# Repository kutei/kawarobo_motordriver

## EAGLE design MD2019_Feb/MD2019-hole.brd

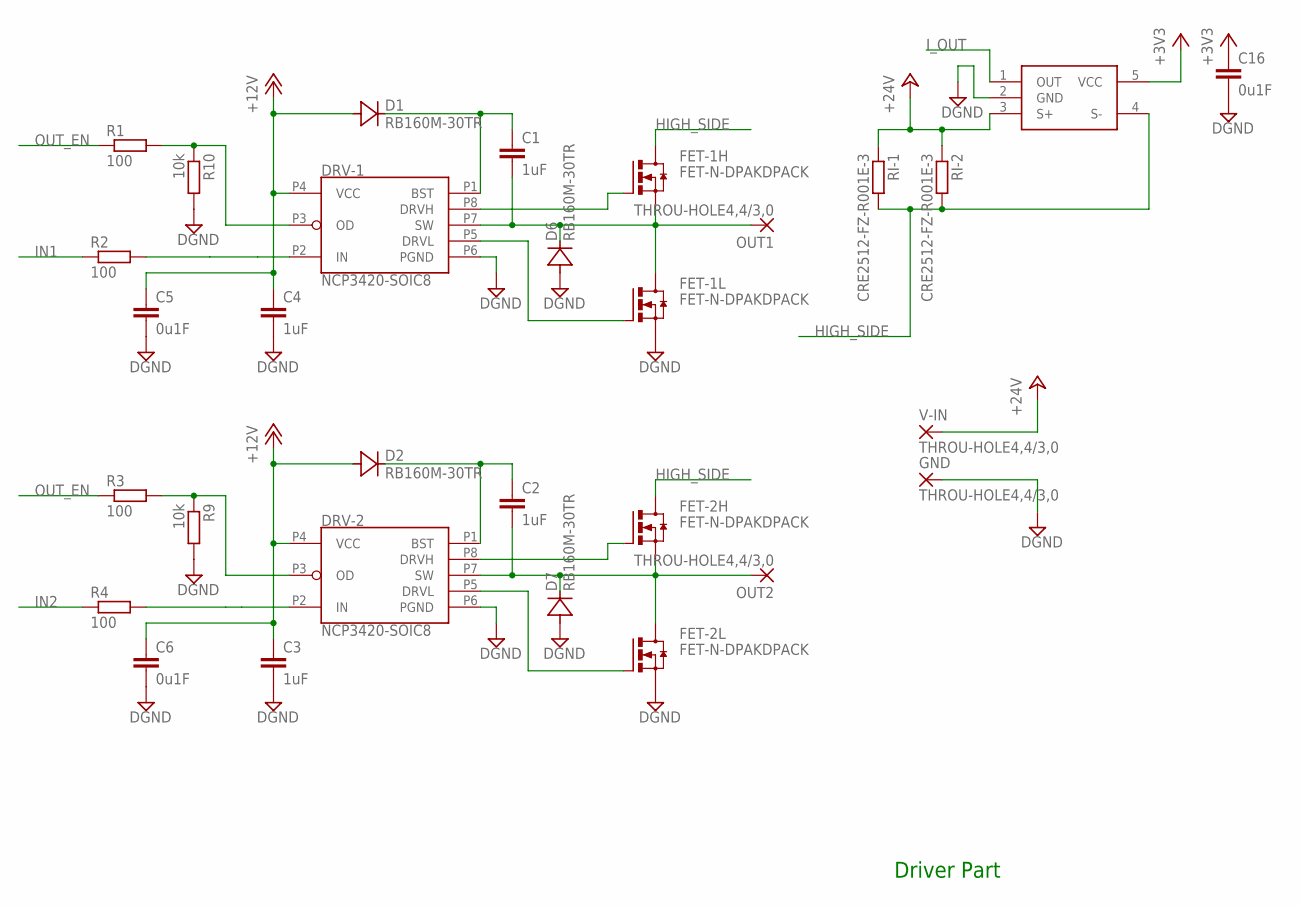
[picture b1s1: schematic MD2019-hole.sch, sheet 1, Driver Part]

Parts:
C1, C2, C3, C4: 1uF; C0805
C5, C6, C16: 0u1F; C0805
D1, D2, D6, D7: RB160M-30TR; SOD123
DRV-1, DRV-2: NCP3420-SOIC8; SOIC-8
FET-1H, FET-1L, FET-2H, FET-2L: FET-N-DPAKDPACK; DPACK
GND: THROU-HOLE4,4/3,0; 4,4/3,0
I_SEN: ZXCT108; SOT25
OUT1, OUT2: THROU-HOLE4,4/3,0; 4,4/3,0
R1, R2, R3, R4: 100; R0603
R9, R10: 10k; R0603
RI-1, RI-2: CRE2512-FZ-R001E-3; CRE2512-R001
V-IN: THROU-HOLE4,4/3,0; 4,4/3,0

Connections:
+3V3: C16.1, I_SEN.5 (VCC); also elsewhere on the board
+12V: C3.1, C4.1, C5.1, C6.1, D1.A, D2.A, DRV-1.P4 (VCC), DRV-2.P4 (VCC); also elsewhere on the board
+24V: I_SEN.3 (S+), RI-1.P$1 (1), RI-2.P$1 (1), V-IN.1; also elsewhere on the board
DGND: C3.2, C4.2, C5.2, C6.2, C16.2, D6.A, D7.A, DRV-1.P6 (PGND), DRV-2.P6 (PGND), FET-1L.3 (S), FET-2L.3 (S), GND.1, I_SEN.2 (GND), R9.2, R10.2; also elsewhere on the board
HIGH_SIDE: FET-1H.4 (D), FET-2H.4 (D), I_SEN.4 (S-), RI-1.P$2 (2), RI-2.P$2 (2)
IN1: R2.1; also elsewhere on the board
IN2: R4.1; also elsewhere on the board
I_OUT: I_SEN.1 (OUT); also elsewhere on the board
unnamed: C1.2, D6.C, DRV-1.P7 (SW), FET-1H.3 (S), FET-1L.4 (D), OUT1.1
unnamed: C1.1, D1.C, DRV-1.P1 (BST)
unnamed: DRV-1.P8 (DRVH), FET-1H.1 (G)
unnamed: DRV-1.P5 (DRVL), FET-1L.1 (G)
unnamed: C2.2, D7.C, DRV-2.P7 (SW), FET-2H.3 (S), FET-2L.4 (D), OUT2.1
unnamed: C2.1, D2.C, DRV-2.P1 (BST)
unnamed: DRV-2.P2 (IN), R4.2
unnamed: DRV-2.P8 (DRVH), FET-2H.1 (G)
unnamed: DRV-2.P5 (DRVL), FET-2L.1 (G)
unnamed: DRV-2.P3 (OD), R3.2, R9.1
unnamed: DRV-1.P2 (IN), R2.2
unnamed: DRV-1.P3 (OD), R1.2, R10.1
OUT_EN: R1.1, R3.1; also elsewhere on the board

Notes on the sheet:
Driver Part

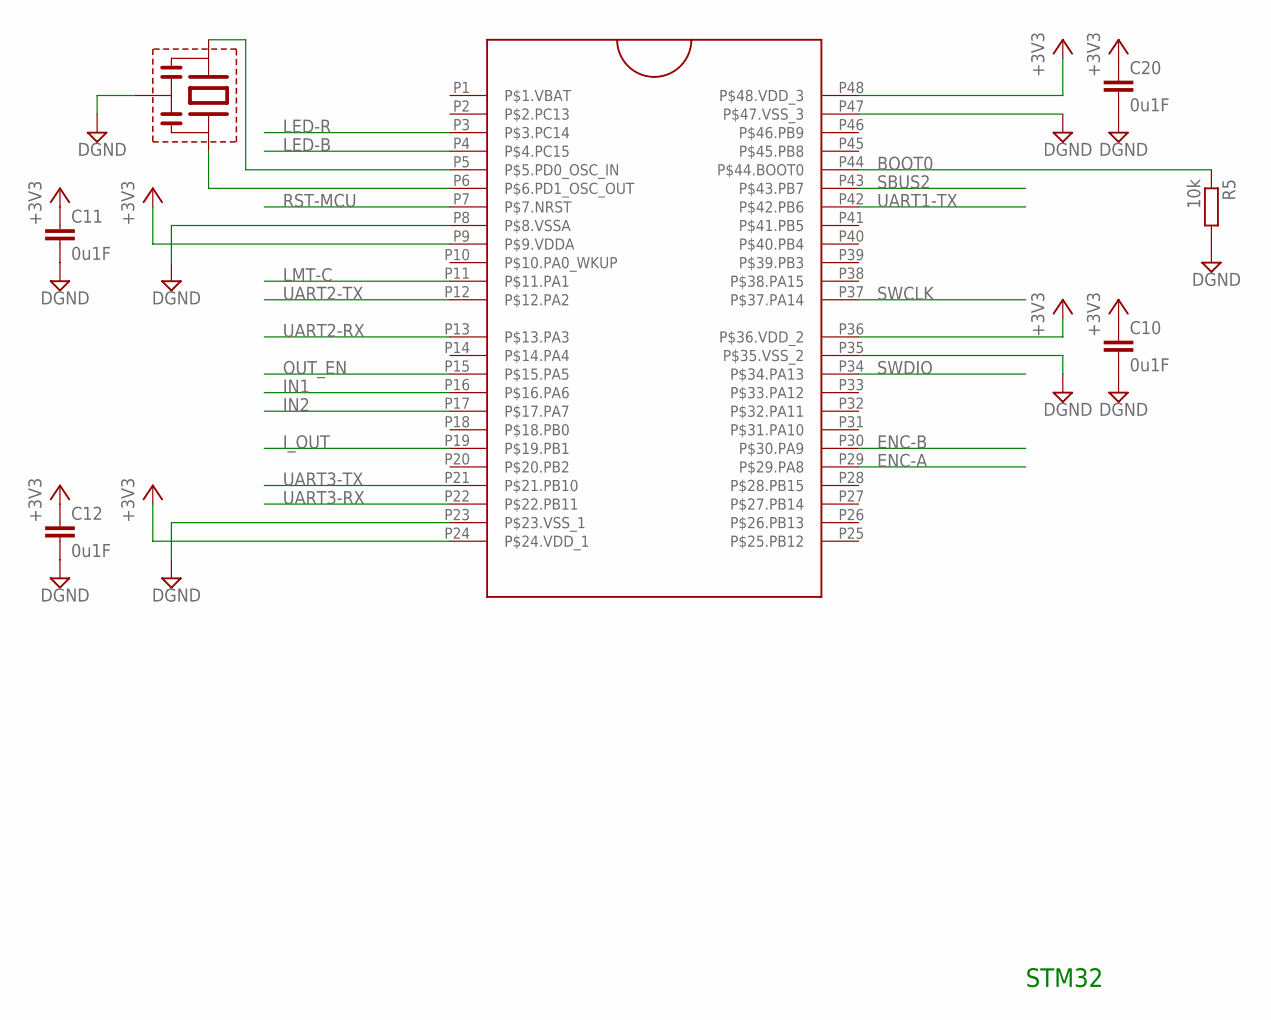
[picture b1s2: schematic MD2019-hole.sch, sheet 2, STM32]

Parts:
C10, C11, C12, C20: 0u1F; C0805
OSC: CERALOCK; CSTCE
R5: 10k; R0603
U$11: STM32F1038; LQFP48_F103

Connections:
+3V3: C10.1, C11.1, C12.1, C20.1, U$11.P9 (P$9.VDDA), U$11.P24 (P$24.VDD_1), U$11.P36 (P$36.VDD_2), U$11.P48 (P$48.VDD_3); also elsewhere on the board
BOOT0: R5.1, U$11.P44 (P$44.BOOT0)
DGND: C10.2, C11.2, C12.2, C20.2, OSC.P$3, R5.2, U$11.P8 (P$8.VSSA), U$11.P23 (P$23.VSS_1), U$11.P35 (P$35.VSS_2), U$11.P47 (P$47.VSS_3); also elsewhere on the board
ENC-A: U$11.P29 (P$29.PA8); also elsewhere on the board
ENC-B: U$11.P30 (P$30.PA9); also elsewhere on the board
IN1: U$11.P16 (P$16.PA6); also elsewhere on the board
IN2: U$11.P17 (P$17.PA7); also elsewhere on the board
I_OUT: U$11.P19 (P$19.PB1); also elsewhere on the board
LED-B: U$11.P4 (P$4.PC15); also elsewhere on the board
LED-R: U$11.P3 (P$3.PC14); also elsewhere on the board
LMT-C: U$11.P11 (P$11.PA1); also elsewhere on the board
unnamed: OSC.P$1, U$11.P5 (P$5.PD0_OSC_IN)
unnamed: OSC.P$2, U$11.P6 (P$6.PD1_OSC_OUT)
OUT_EN: U$11.P15 (P$15.PA5); also elsewhere on the board
RST-MCU: U$11.P7 (P$7.NRST); also elsewhere on the board
SBUS2: U$11.P43 (P$43.PB7); also elsewhere on the board
SWCLK: U$11.P37 (P$37.PA14); also elsewhere on the board
SWDIO: U$11.P34 (P$34.PA13); also elsewhere on the board
UART1-TX: U$11.P42 (P$42.PB6)
UART2-RX: U$11.P13 (P$13.PA3); also elsewhere on the board
UART2-TX: U$11.P12 (P$12.PA2); also elsewhere on the board
UART3-RX: U$11.P22 (P$22.PB11); also elsewhere on the board
UART3-TX: U$11.P21 (P$21.PB10); also elsewhere on the board

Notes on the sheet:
STM32

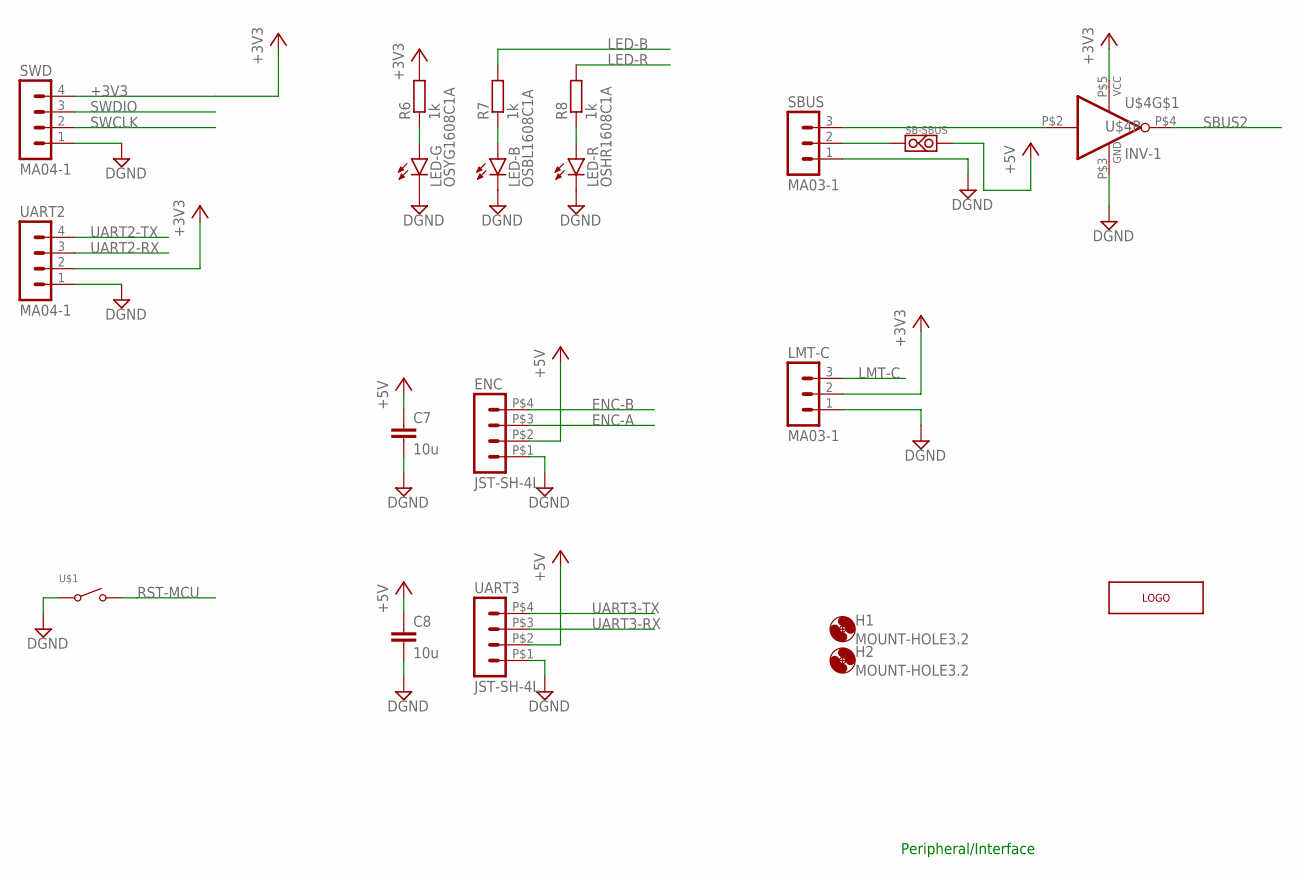
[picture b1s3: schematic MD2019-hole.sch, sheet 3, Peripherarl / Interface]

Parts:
C7, C8: 10u; C0805K
ENC: JST-SH-4L
H1, H2: MOUNT-HOLE3.2; 3,2
LED-B: OSBL1608C1A; CHIPLED_0603
LED-G: OSYG1608C1A; CHIPLED_0603
LED-R: OSHR1608C1A; CHIPLED_0603
LMT-C: MA03-1
R6, R7, R8: 1k; R0603
SB-SBUS: SHORT-PINLAND; SHORT-LAND
SBUS: MA03-1
SWD: MA04-1
U$1: TACTILE-SMALL
U$3: LOGOKUTEI2; LOGO_KUTEI2
U$4: INV-1; CMPAK-5
UART2: MA04-1
UART3: JST-SH-4L

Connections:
+3V3: LMT-C.2, R6.2, SWD.4, U$4.P$5 (VCC), UART2.2; also elsewhere on the board
+5V: C7.1, C8.1, ENC.P$2 (2), SB-SBUS.FROM, UART3.P$2 (2); also elsewhere on the board
DGND: C7.2, C8.2, ENC.P$1 (1), LED-B.C, LED-G.C, LED-R.C, LMT-C.1, SBUS.1, SWD.1, U$1.P$1, U$4.P$3 (GND), UART2.1, UART3.P$1 (1); also elsewhere on the board
ENC-A: ENC.P$3 (3); also elsewhere on the board
ENC-B: ENC.P$4 (4); also elsewhere on the board
LED-B: R7.2; also elsewhere on the board
LED-R: R8.2; also elsewhere on the board
LMT-C: LMT-C.3; also elsewhere on the board
unnamed: SBUS.3, U$4.P$2 (I)
unnamed: SB-SBUS.TO, SBUS.2
unnamed: LED-R.A, R8.1
unnamed: LED-G.A, R6.1
unnamed: LED-B.A, R7.1
RST-MCU: U$1.P$2; also elsewhere on the board
SBUS2: U$4.P$4 (O); also elsewhere on the board
SWCLK: SWD.2; also elsewhere on the board
SWDIO: SWD.3; also elsewhere on the board
UART2-RX: UART2.3; also elsewhere on the board
UART2-TX: UART2.4; also elsewhere on the board
UART3-RX: UART3.P$3 (3); also elsewhere on the board
UART3-TX: UART3.P$4 (4); also elsewhere on the board

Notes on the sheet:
Peripheral/Interface

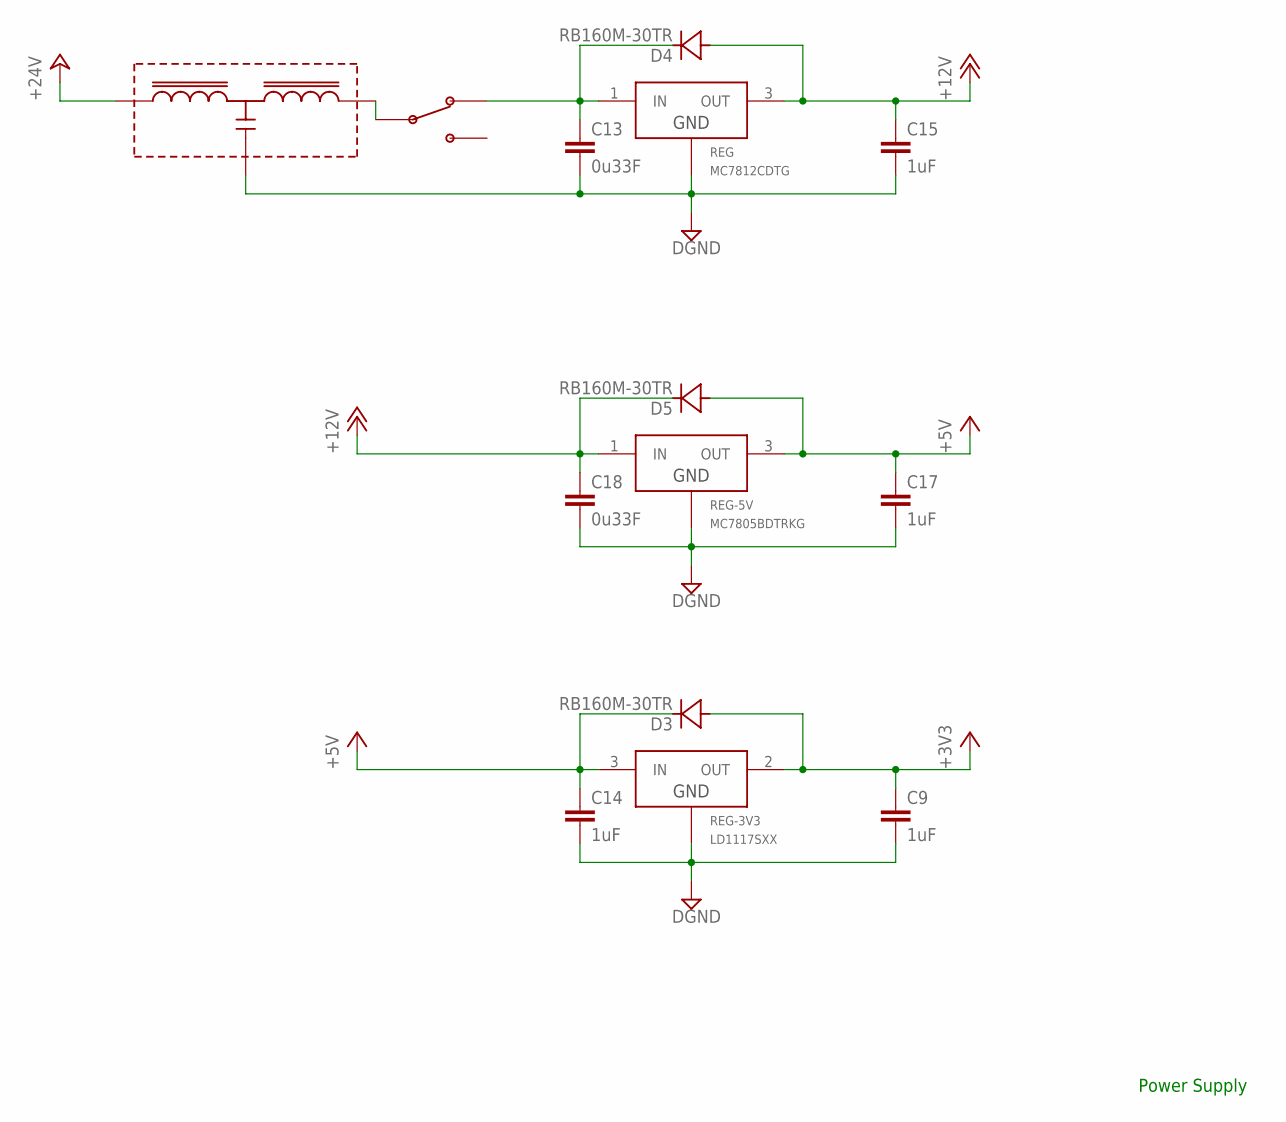
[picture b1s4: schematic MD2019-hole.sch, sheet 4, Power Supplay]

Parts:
C9, C14, C15, C17: 1uF; C0805
C13, C18: 0u33F; C0805
D3, D4, D5: RB160M-30TR; SOD123
FLT1: EMI-ACHXX4518-L; ACH4518-L
PWR-SW: SW-SPDT; SSSS213202
REG: MC7812CDTG; DPACK
REG-3V3: LD1117SXX; SOT223
REG-5V: MC7805BDTRKG; DPACK

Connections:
+3V3: C9.1, D3.A, REG-3V3.2 (OUT); also elsewhere on the board
+5V: C14.1, C17.1, D3.C, D5.A, REG-3V3.3 (IN), REG-5V.3 (OUT); also elsewhere on the board
+12V: C15.1, C18.1, D4.A, D5.C, REG.3 (OUT), REG-5V.1 (IN); also elsewhere on the board
+24V: FLT1.P$1; also elsewhere on the board
DGND: C9.2, C13.2, C14.2, C15.2, C17.2, C18.2, FLT1.P$2, REG.4 (GND), REG-3V3.1 (GND), REG-3V3.4 (GND), REG-5V.4 (GND); also elsewhere on the board
unnamed: FLT1.P$3, PWR-SW.P$2, PWR-SW.P$5
unnamed: C13.1, D4.C, PWR-SW.P$3, PWR-SW.P$6, REG.1 (IN)

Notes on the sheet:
Power Supply

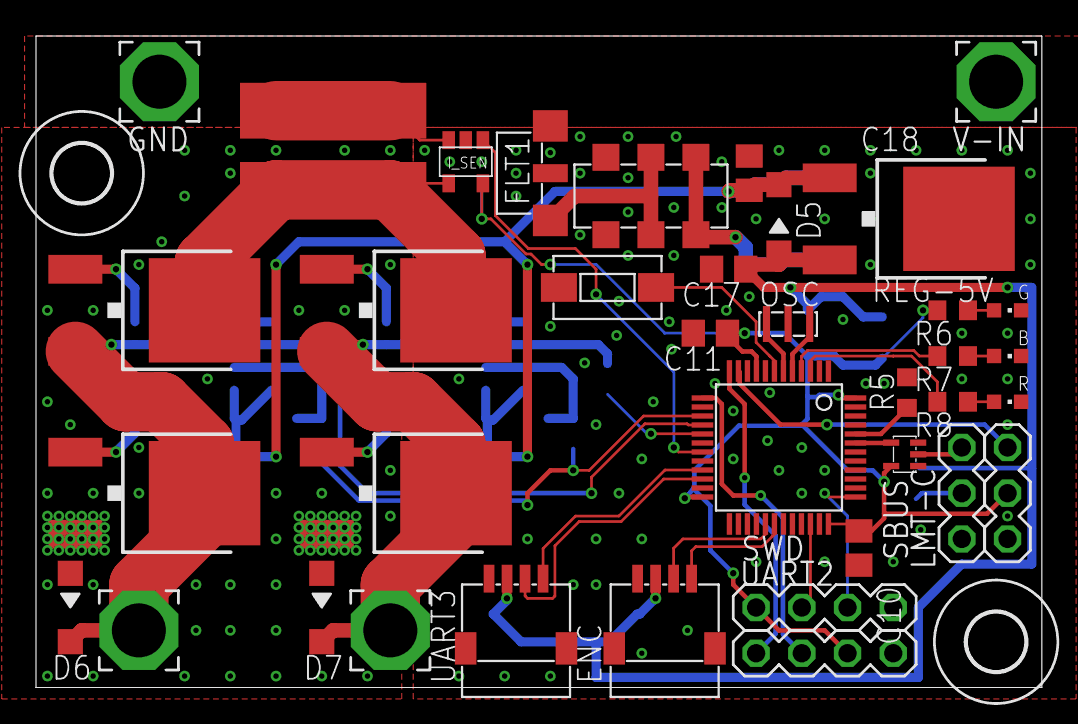
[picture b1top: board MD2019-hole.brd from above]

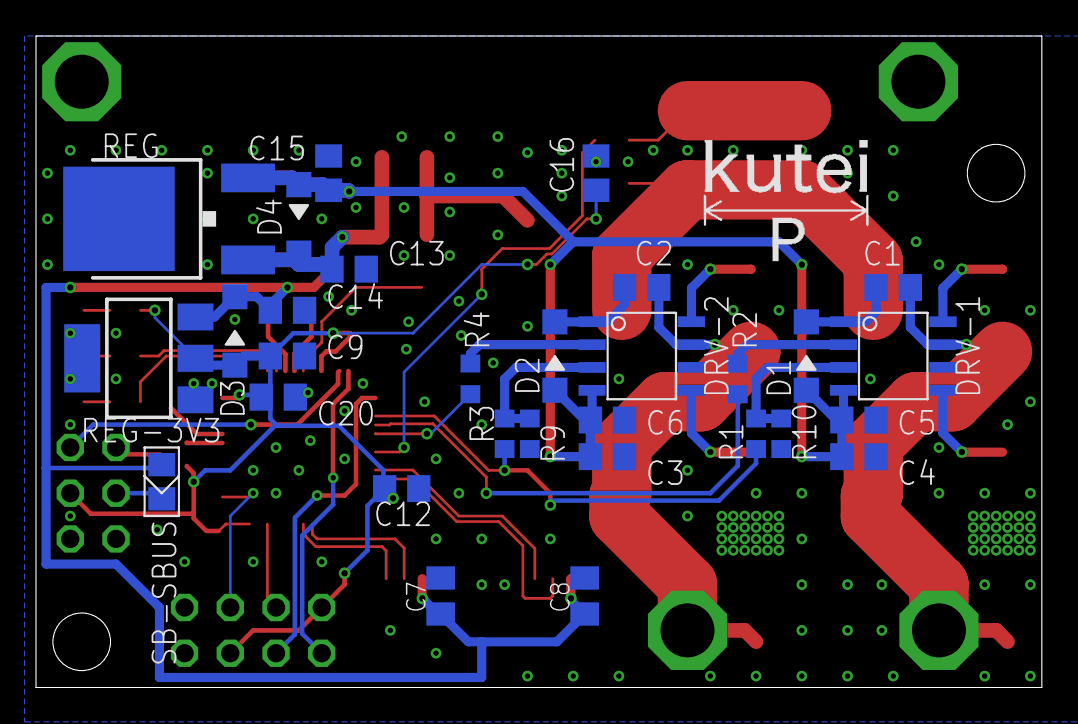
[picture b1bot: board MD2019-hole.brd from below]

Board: 2 copper layers, 55.9 x 36.2 mm, 71 parts (31 on the bottom side), 45 nets.

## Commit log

2019-11-24 gitignoreを追加
2019-11-24 MD2019_Febを追加
